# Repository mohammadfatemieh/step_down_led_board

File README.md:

This is a small Pi hat that has simple goals:

- Power the Pi off 12 or 24V
- Control some LEDs (digital output)

Either turn channels fully on and off, or use pigpiod to emulate reasonable PWM support.

Check the branch list for other versions.

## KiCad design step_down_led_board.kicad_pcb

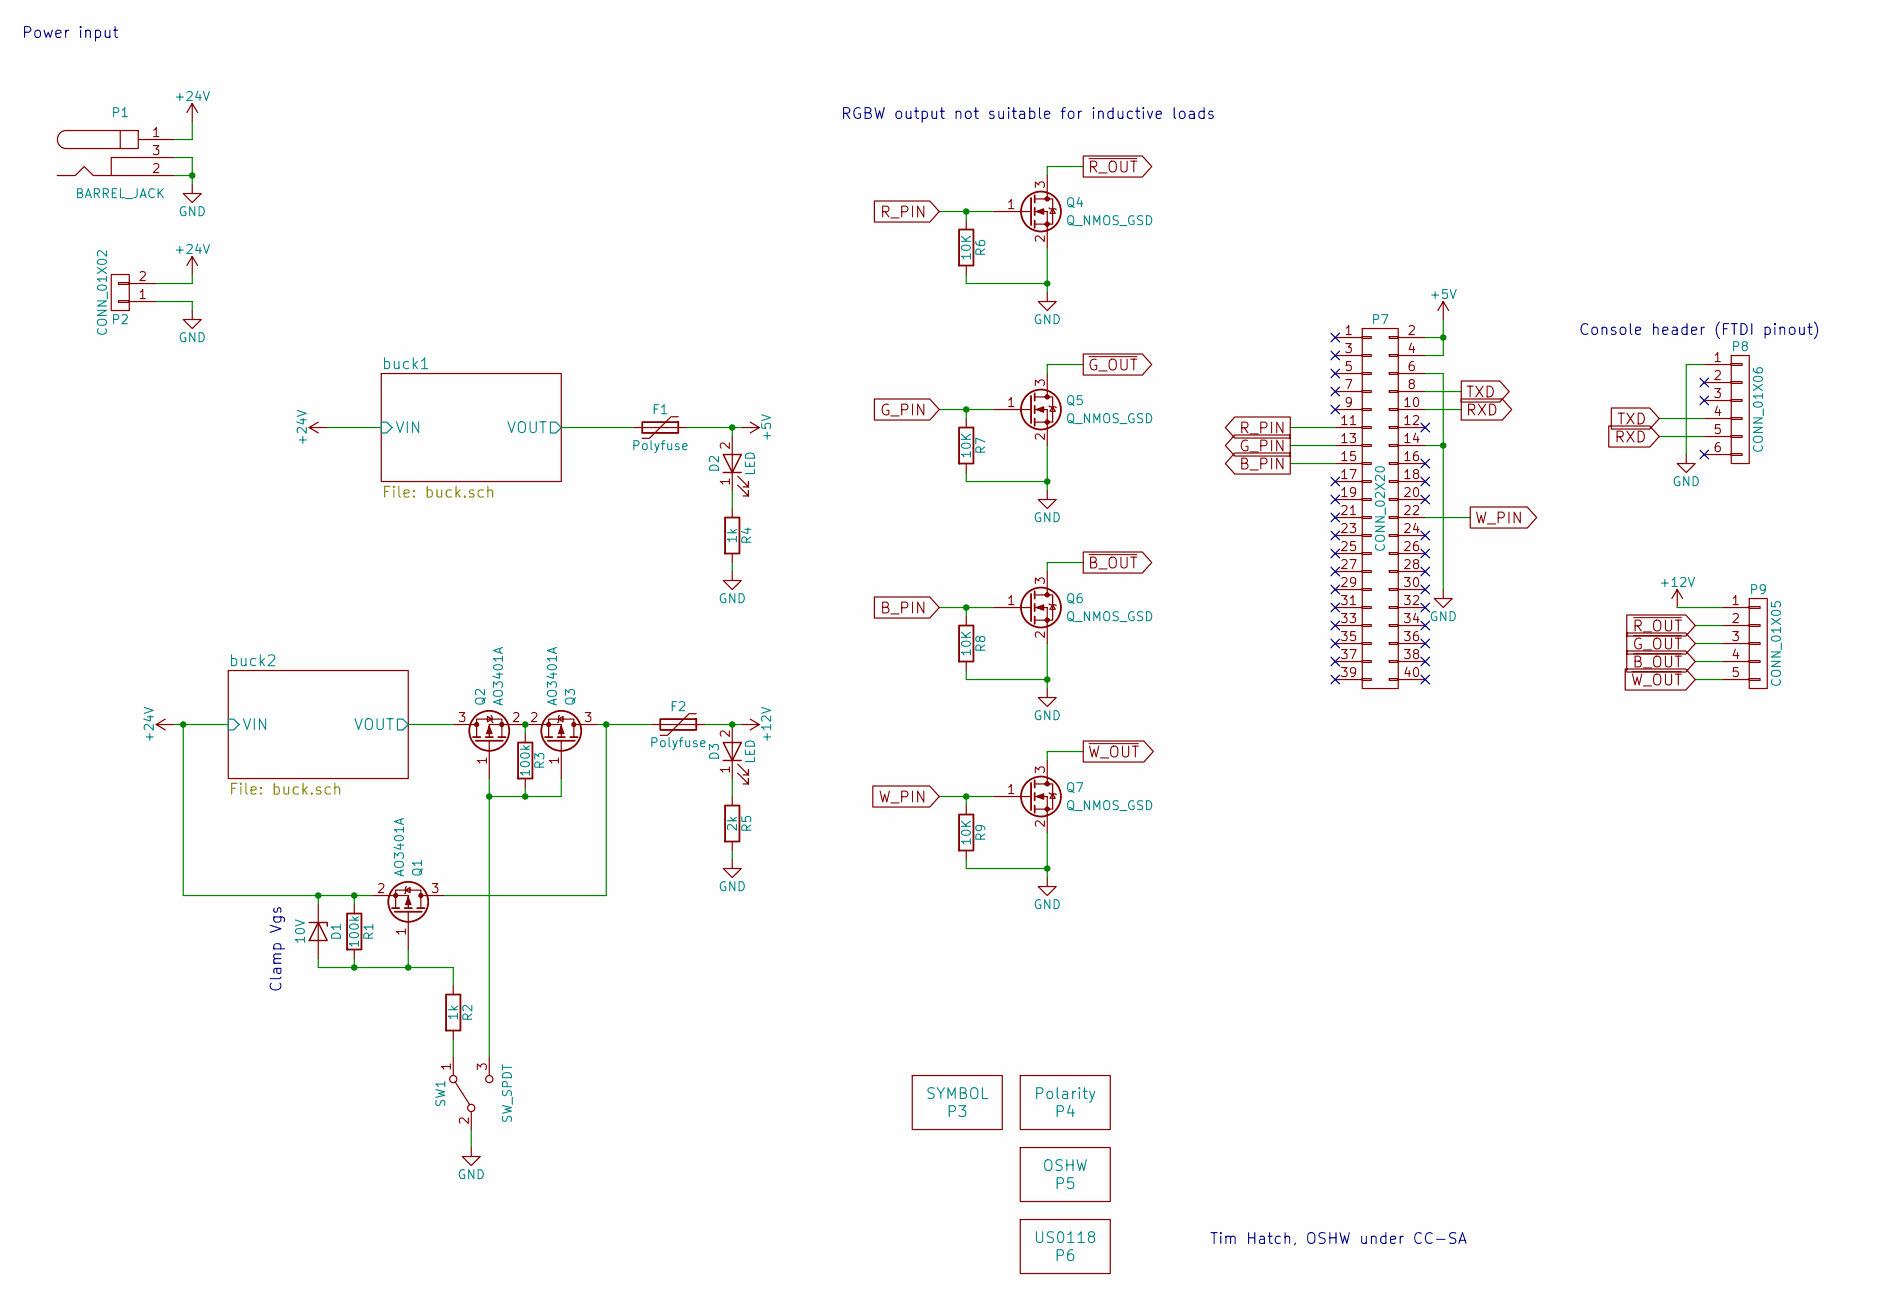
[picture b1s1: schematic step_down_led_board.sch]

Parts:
D1: 10V; D_SOD-123
D2, D3: LED; LED_0805
F1, F2: Polyfuse; R_1812
P1: BARREL_JACK
P2: CONN_01X02; Molex_KK-6410-02_02x2.54mm_Straight
P3: SYMBOL; Pi_Zero
P4: Polarity; Polarity_Center_Positive_2mm_SilkScreen
P5: OSHW; OSHW-Logo_11.4x12mm_SilkScreen
P6: US0118; OSHW_Mono_0.25_Scale
P7: CONN_02X20; Pin_Header_Straight_2x20_Pitch2.54mm
P8: CONN_01X06; Pin_Header_Straight_1x06_Pitch2.54mm
P9: CONN_01X05; JST_XH_B05B-XH-A_05x2.50mm_Straight
Q1, Q2, Q3: AO3401A; SOT-23
Q4, Q5, Q6, Q7: Q_NMOS_GSD; SOT-23_Handsoldering
R1, R3: 100k; R_0603
R2, R4: 1k; R_0603
R5: 2k; R_0603
R6, R7, R8, R9: 10K; R_0603
SW1: SW_SPDT; SW_SPDT_PCM12

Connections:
+5V: D2.2 (A), F1.1, P7.2, P7.4
+12V: D3.2 (A), F2.1, P9.1
+24V: D1.1 (K), P1.1, P2.2, Q1.2 (S), R1.1; also elsewhere on the board
/buck1/VOUT: F1.2; also elsewhere on the board
/buck2/VOUT: Q2.3 (D); also elsewhere on the board
B_PIN: P7.15, Q6.1 (G), R8.1
GND: P1.2, P1.3, P2.1, P7.6, P7.14, P8.1, Q4.2 (S), Q5.2 (S), Q6.2 (S), Q7.2 (S), R4.2, R5.2, R6.2, R7.2, R8.2, R9.2, SW1.2 (B); also elsewhere on the board
G_PIN: P7.13, Q5.1 (G), R7.1
unnamed: D1.2 (A), Q1.1 (G), R1.2, R2.1
unnamed: D2.1 (K), R4.1
unnamed: D3.1 (K), R5.1
unnamed: F2.2, Q1.3 (D), Q3.3 (D)
unnamed: Q2.1 (G), Q3.1 (G), R3.2, SW1.3 (C)
unnamed: Q2.2 (S), Q3.2 (S), R3.1
unnamed: R2.2, SW1.1 (A)
RXD: P7.10, P8.5
R_PIN: P7.11, Q4.1 (G), R6.1
TXD: P7.8, P8.4
W_PIN: P7.22, Q7.1 (G), R9.1
~B_OUT: P9.4, Q6.3 (D)
~G_OUT: P9.3, Q5.3 (D)
~R_OUT: P9.2, Q4.3 (D)
~W_OUT: P9.5, Q7.3 (D)

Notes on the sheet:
RGBW output not suitable for inductive loads
Power input
Console header (FTDI pinout)
Tim Hatch, OSHW under CC-SA
Clamp Vgs

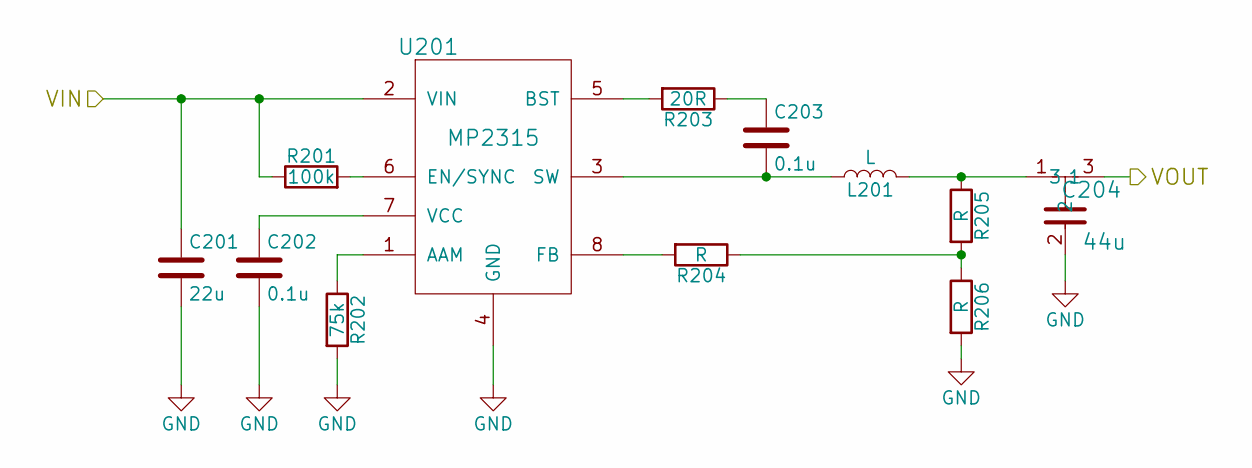
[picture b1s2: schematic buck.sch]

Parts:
C201: 22u; C_1206
C202, C203: 0.1u; C_0603
C304: 44u; C_1206_NetTie
L201: L; L_Taiyo-Yuden_MD-5050
R201: 100k; R_0603
R202: 75k; R_0603
R203: 20R; R_0603
R204, R205, R206: R; R_0603
U201: MP2315; SOT-23-8

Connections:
+24V: C201.1, R201.1, U201.2 (VIN); also elsewhere on the board
/buck2/VOUT: C304.3; also elsewhere on the board
GND: C201.2, C202.2, C304.2, R202.2, R206.2, U201.4 (GND); also elsewhere on the board
unnamed: C202.1, U201.7 (VCC)
unnamed: C203.1, R203.1
unnamed: C203.2, L201.1, U201.3 (SW)
unnamed: R201.2, U201.6 (EN/SYNC)
unnamed: R202.1, U201.1 (AAM)
unnamed: R203.2, U201.5 (BST)
unnamed: R204.1, R205.2, R206.1
unnamed: R204.2, U201.8 (FB)

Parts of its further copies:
C204: 44u; C_1206_NetTie
C301: 22u; C_1206
C302, C303: 0.1u; C_0603
L301: L; L_Taiyo-Yuden_MD-5050
R301: 100k; R_0603
R302: 75k; R_0603
R303: 20R; R_0603
R304, R305, R306: R; R_0603
U301: MP2315; SOT-23-8

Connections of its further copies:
+24V: C301.1, R301.1, U301.2 (VIN); also elsewhere on the board
/buck1/VOUT: C204.3; also elsewhere on the board
GND: C204.2, C301.2, C302.2, R302.2, R306.2, U301.4 (GND); also elsewhere on the board
unnamed: C302.1, U301.7 (VCC)
unnamed: C303.1, R303.1
unnamed: C303.2, L301.1, U301.3 (SW)
unnamed: R301.2, U301.6 (EN/SYNC)
unnamed: R302.1, U301.1 (AAM)
unnamed: R303.2, U301.5 (BST)
unnamed: R304.1, R305.2, R306.1
unnamed: R304.2, U301.8 (FB)

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
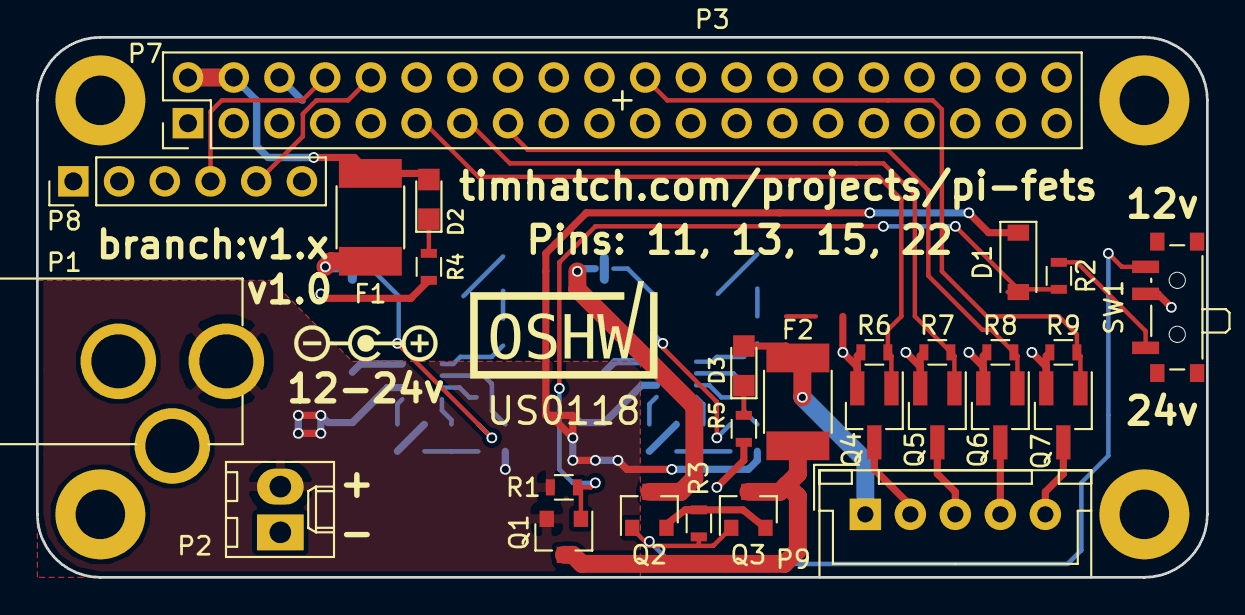
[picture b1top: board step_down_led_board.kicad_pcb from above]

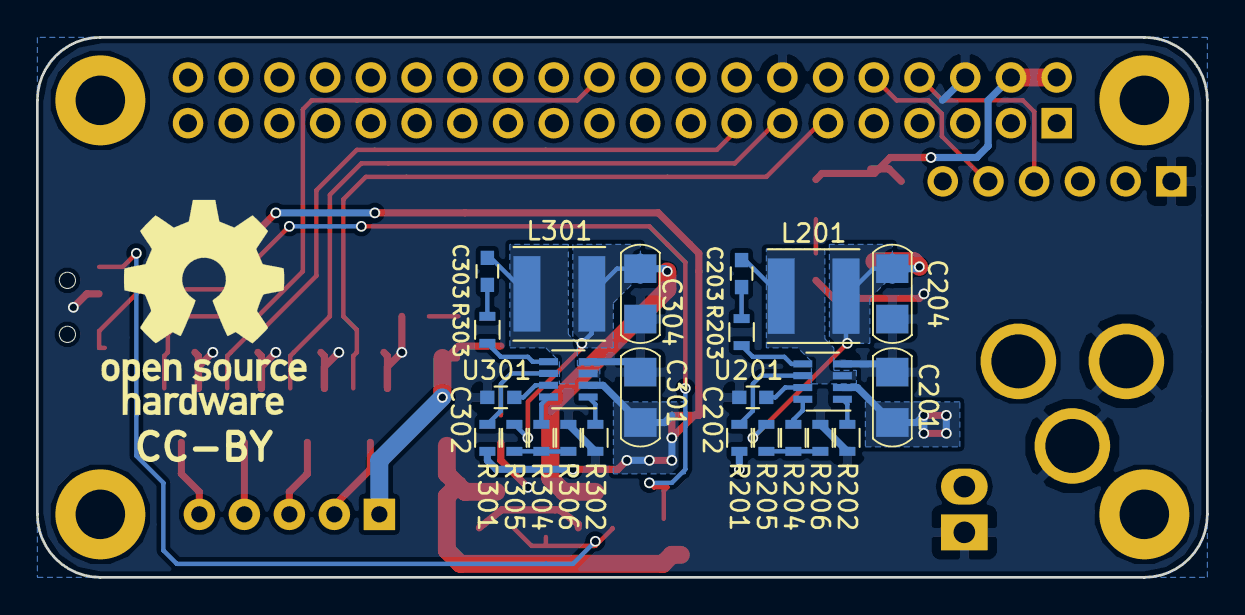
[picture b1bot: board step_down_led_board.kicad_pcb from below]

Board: 2 copper layers, 65.0 x 30.0 mm, 55 parts (25 on the bottom side), 41 nets.

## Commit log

2017-03-29 Checkpoint spacious board with RGBW support.
2017-03-29 remove extra libs
2017-03-29 Add license and readme
2017-03-29 Use my solder jumper part.
    Also fix some trace stragglers and silkscreen.
2017-03-29 Add v0.2 text
2017-03-29 Update assembly text
2018-02-27 Include buck converter on board.
2018-02-28 Switch submodule url
2018-02-28 Update submodules (fix pi zero layers, add oshw mark)
2018-03-01 Massive changes, including makefile
2018-03-07 Update partsbin submodule
2018-03-07 Update OSH Certification
2018-03-07 Switch license, add render

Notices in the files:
step_down_led_board.kicad_pcb:
CC-BY
